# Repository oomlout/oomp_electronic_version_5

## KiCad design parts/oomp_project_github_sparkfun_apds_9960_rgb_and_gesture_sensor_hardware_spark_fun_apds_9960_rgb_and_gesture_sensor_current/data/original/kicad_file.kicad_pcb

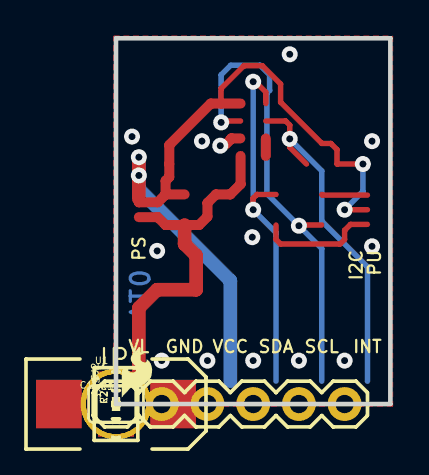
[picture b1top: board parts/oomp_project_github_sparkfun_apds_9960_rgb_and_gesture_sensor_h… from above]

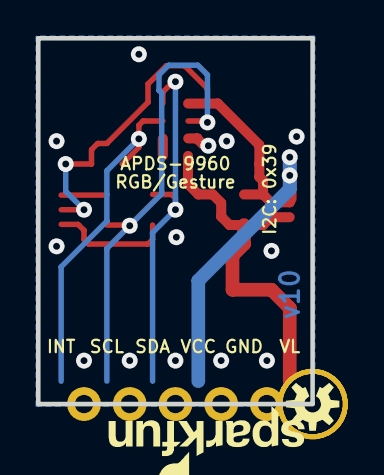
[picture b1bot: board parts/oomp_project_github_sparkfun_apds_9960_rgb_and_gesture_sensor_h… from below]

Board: 4 copper layers, 15.2 x 20.3 mm, 19 parts (2 on the bottom side), 9 nets.

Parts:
C1: 100uF; EIA7343
C2, C3: 1.0uF; 0603-CAP
FID1, FID2: FIDUCIAL1X2; FIDUCIAL-1X2
FRAME1: FRAME-LETTER; CREATIVE_COMMONS
JP1: 1X06
LOGO1: SFE_LOGO_FLAME.1_INCH; SFE_LOGO_FLAME_.1
LOGO2: OSHW-LOGOS; OSHW-LOGO-S
R1: 10k; 0603-RES
R2, R3: 4.7k; 0603
R4: DNP; 0603-RES
SJ1: SJ_3_PASTE1&2&3
SJ2: SOLDERJUMPERNC; SJ_2S
STANDOFF1, STANDOFF2: STAND-OFF
U1: APDS-9960
U$1: SFE_LOGO_NAME_FLAME.1_INCH; SFE_LOGO_NAME_FLAME_.1

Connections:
GND: C1.C, C2.2, C3.2, JP1.2, U1.6
INT: JP1.6, R1.1, U1.2
unnamed: R2.2, SJ1.3
unnamed: R3.2, SJ1.1
unnamed: U1.3, U1.4
SCL: JP1.5, R3.1, U1.7
SDA: JP1.4, R2.1, U1.1
VCC: C3.1, JP1.3, R1.2, R4.2, SJ1.2, SJ2.2, U1.8
VL: C1.A, C2.1, JP1.1, R4.1, SJ2.1, U1.5

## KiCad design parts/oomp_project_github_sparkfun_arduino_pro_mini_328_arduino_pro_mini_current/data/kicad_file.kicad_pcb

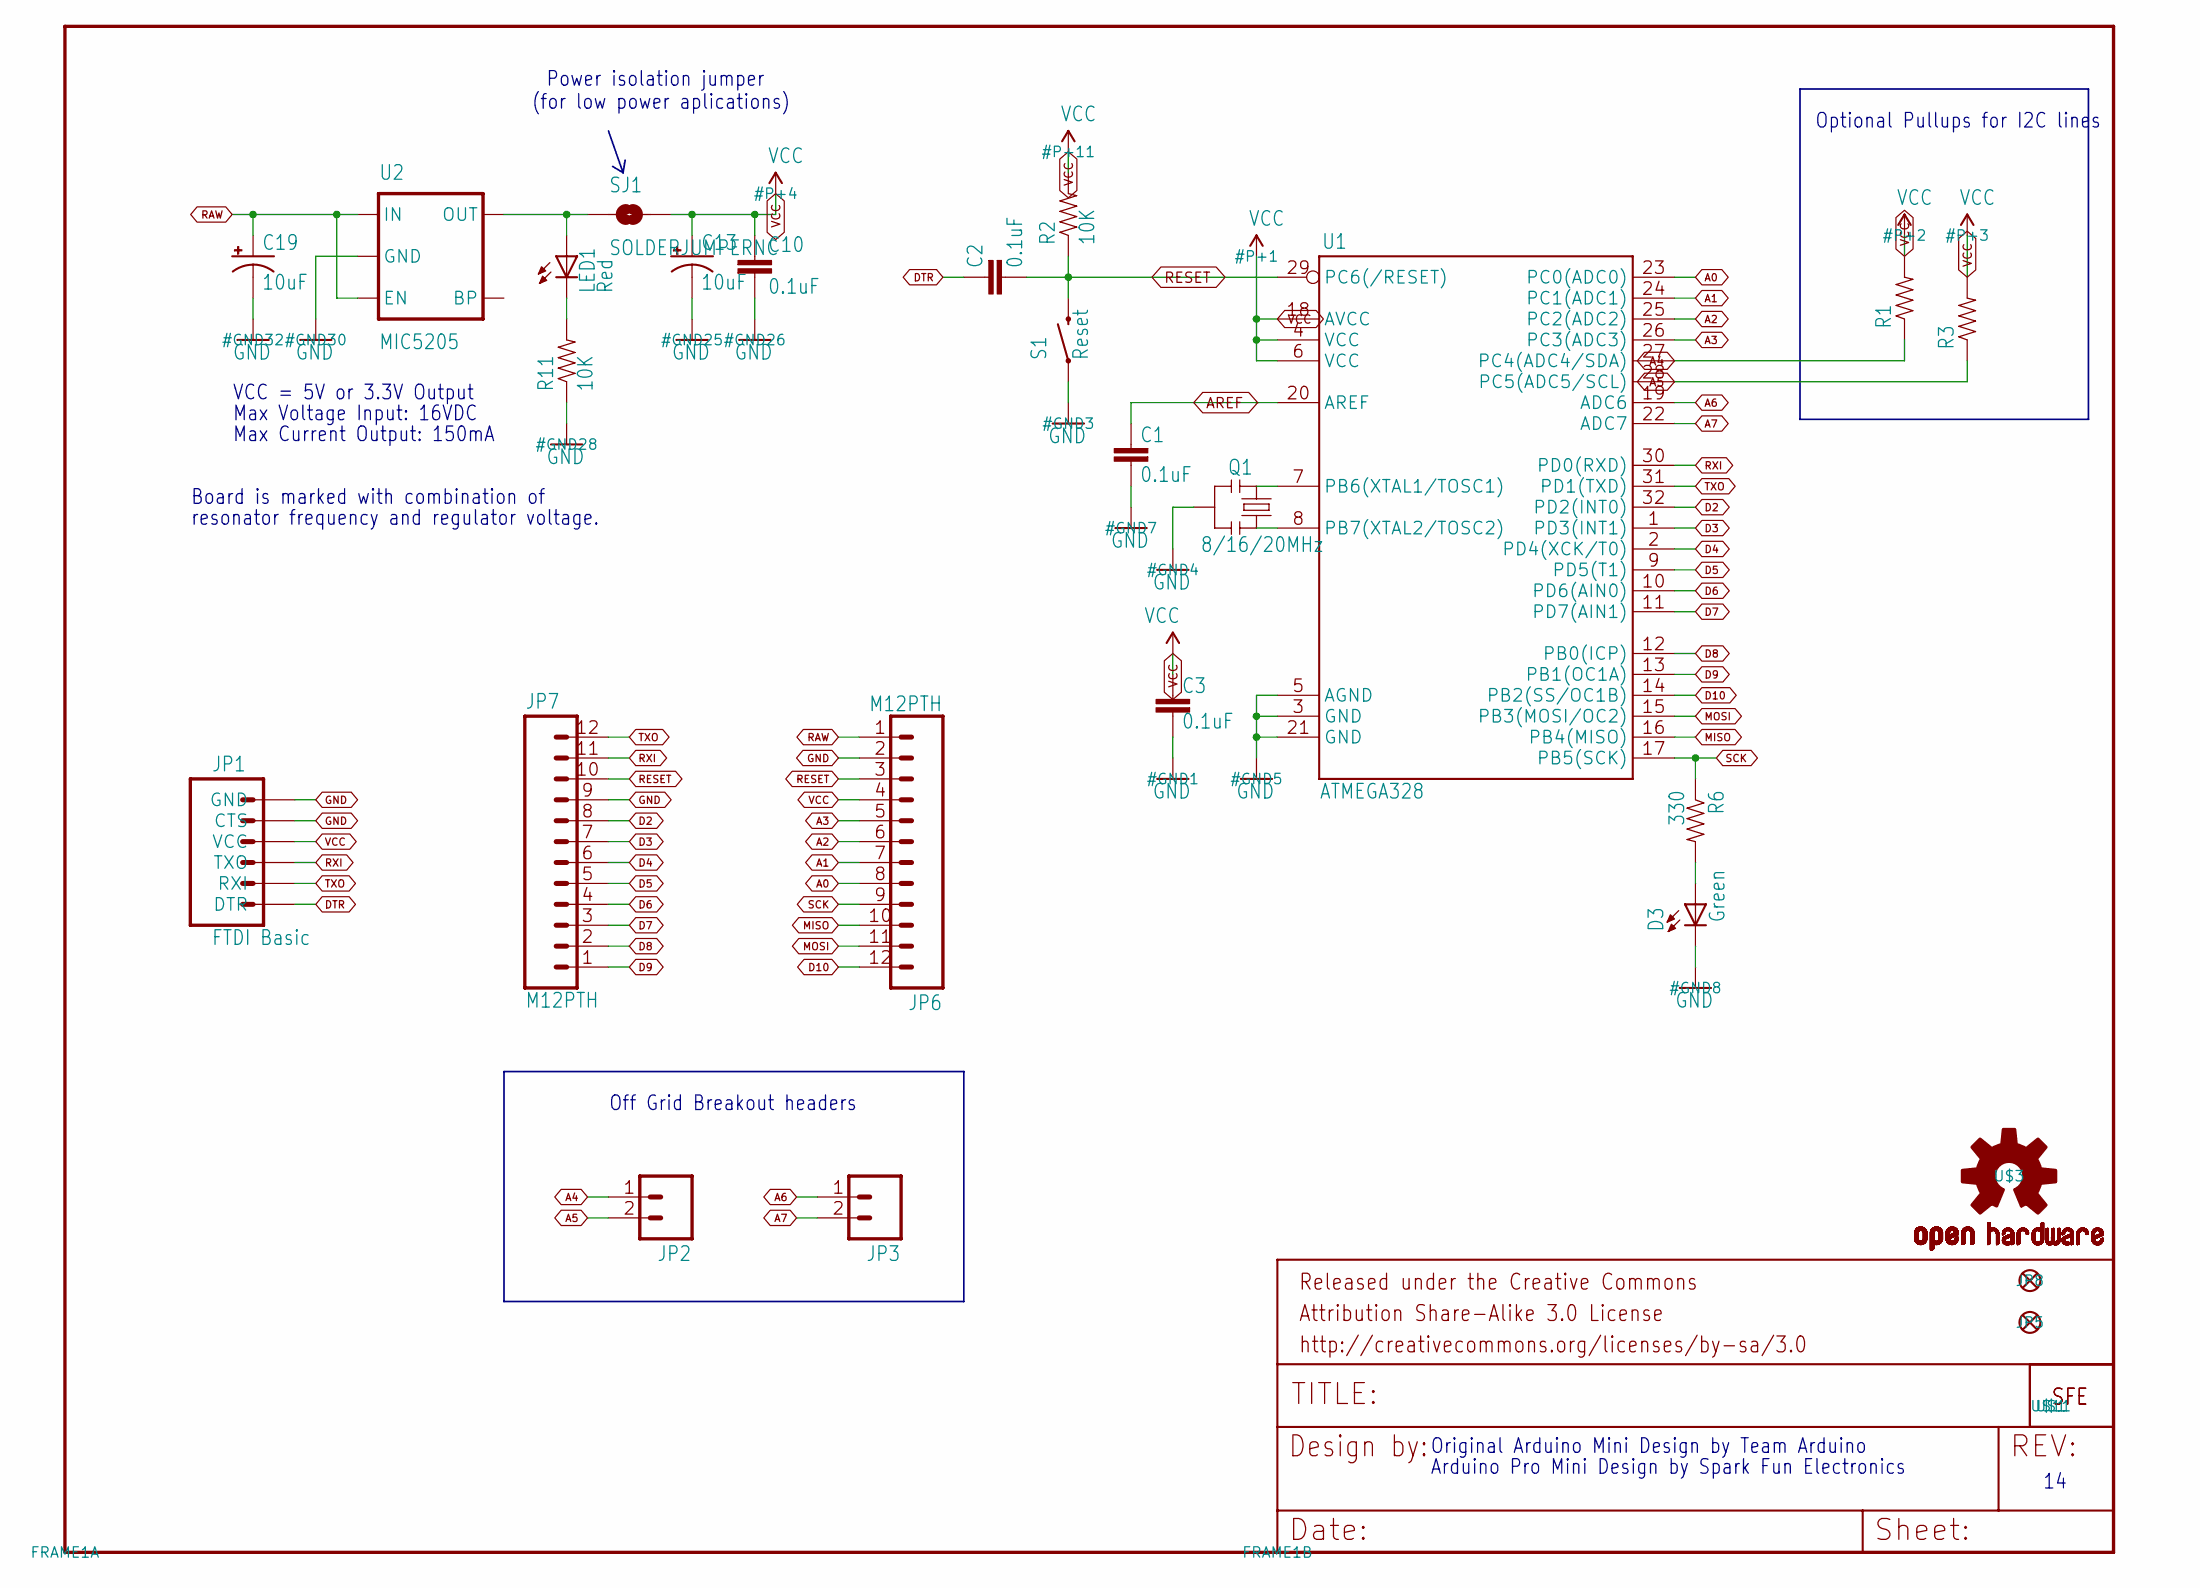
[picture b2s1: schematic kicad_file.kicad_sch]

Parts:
C1, C2, C3, C10: 0.1uF; 0603-CAP
C13, C19: 10uF; EIA3216
D3: Green; 0603-LED-ALT1
FRAME1: FRAME-LETTER; CREATIVE_COMMONS
JP1: FTDI Basic; 1X06
JP2, JP3: M02PTH; 1X02
JP5, JP8: FIDUCIALUFIDUCIAL; MICRO-FIDUCIAL
JP6, JP7: M12PTH; 1X12
LED1: Red; 0603-LED-ALT1
Q1: 8/16/20MHz; RESONATOR-SMD-1_1
R1, R3: RESISTOR0603-RES; 0603-RES
R2, R11: 10K; 0603-RES
R6: 330; 0603-RES
S1: Reset; TACTILE-SWITCH-SMD-ALT01
SJ1: SOLDERJUMPERNC; SJ_2S
U1: ATMEGA328; TQFP32-08
U2: MIC5205; SOT23-5
U$1: LOGO-SFESK; SFE-LOGO-FLAME
U$3: OSHW-LOGOS; OSHW-LOGO-S
U$11: LOGO-SFENEW; SFE-NEW-WEBLOGO

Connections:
A0: JP6.8, U1.23 (PC0(ADC0))
A1: JP6.7, U1.24 (PC1(ADC1))
A2: JP6.6, U1.25 (PC2(ADC2))
A3: JP6.5, U1.26 (PC3(ADC3))
A4: JP2.1, R1.1, U1.27 (PC4(ADC4/SDA))
A5: JP2.2, R3.1, U1.28 (PC5(ADC5/SCL))
A6: JP3.1, U1.19 (ADC6)
A7: JP3.2, U1.22 (ADC7)
AREF: C1.2, U1.20 (AREF)
D2: JP7.8, U1.32 (PD2(INT0))
D3: JP7.7, U1.1 (PD3(INT1))
D4: JP7.6, U1.2 (PD4(XCK/T0))
D5: JP7.5, U1.9 (PD5(T1))
D6: JP7.4, U1.10 (PD6(AIN0))
D7: JP7.3, U1.11 (PD7(AIN1))
D8: JP7.2, U1.12 (PB0(ICP))
D9: JP7.1, U1.13 (PB1(OC1A))
D10: JP6.12, U1.14 (PB2(SS/OC1B))
DTR: C2.2, JP1.1 (DTR)
GND: C1.1, C3.1, C10.2, C13.C (-), C19.C (-), D3.C, JP1.5 (CTS), JP1.6 (GND), JP6.2, JP7.9, Q1.2, R11.1, S1.1, S1.2 (1), U1.3 (GND), U1.5 (AGND), U1.21 (GND), U2.2 (GND)
MISO: JP6.10, U1.16 (PB4(MISO))
MOSI: JP6.11, U1.15 (PB3(MOSI/OC2))
unnamed: Q1.3, U1.8 (PB7(XTAL2/TOSC2))
unnamed: Q1.1, U1.7 (PB6(XTAL1/TOSC1))
unnamed: LED1.A, SJ1.1, U2.5 (OUT)
unnamed: LED1.C, R11.2
unnamed: D3.A, R6.2
RAW: C19.A (+), JP6.1, U2.1 (IN), U2.3 (EN)
RESET: C2.1, JP6.3, JP7.10, R2.1, S1.3 (2), S1.4 (2), U1.29 (PC6(/RESET))
RXI: JP1.3 (TXO), JP7.11, U1.30 (PD0(RXD))
SCK: JP6.9, R6.1, U1.17 (PB5(SCK))
TXO: JP1.2 (RXI), JP7.12, U1.31 (PD1(TXD))
VCC: C3.2, C10.1, C13.A (+), JP1.4 (VCC), JP6.4, R1.2, R2.2, R3.2, SJ1.2, U1.4 (VCC), U1.6 (VCC), U1.18 (AVCC)

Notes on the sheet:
Power isolation jumper
Off Grid Breakout headers
(for low power aplications)
VCC = 5V or 3.3V Output
Board is marked with combination of
Max Current Output: 150mA
Original Arduino Mini Design by Team Arduino
Max Voltage Input: 16VDC
resonator frequency and regulator voltage.
Arduino Pro Mini Design by Spark Fun Electronics
Optional Pullups for I2C lines

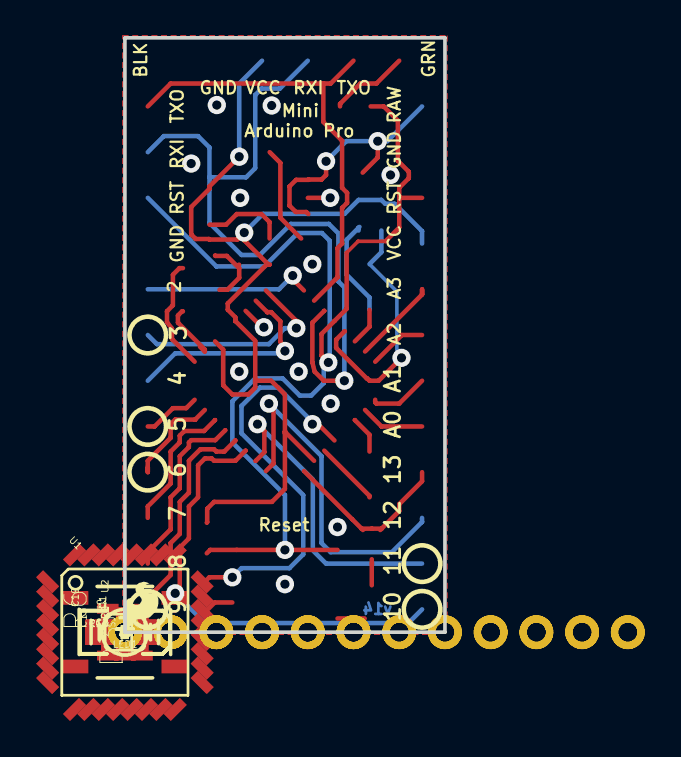
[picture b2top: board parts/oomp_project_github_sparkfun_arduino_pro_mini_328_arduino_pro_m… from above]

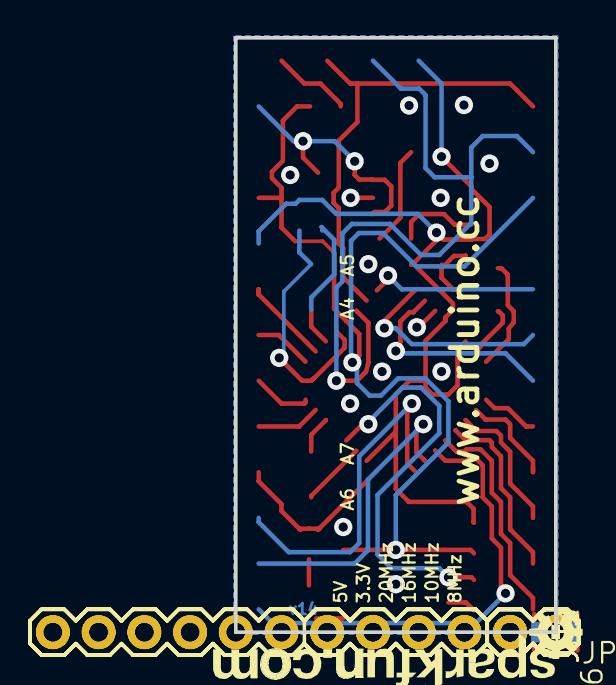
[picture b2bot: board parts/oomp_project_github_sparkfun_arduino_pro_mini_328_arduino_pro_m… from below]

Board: 2 copper layers, 17.8 x 33.0 mm, 29 parts (9 on the bottom side), 33 nets.

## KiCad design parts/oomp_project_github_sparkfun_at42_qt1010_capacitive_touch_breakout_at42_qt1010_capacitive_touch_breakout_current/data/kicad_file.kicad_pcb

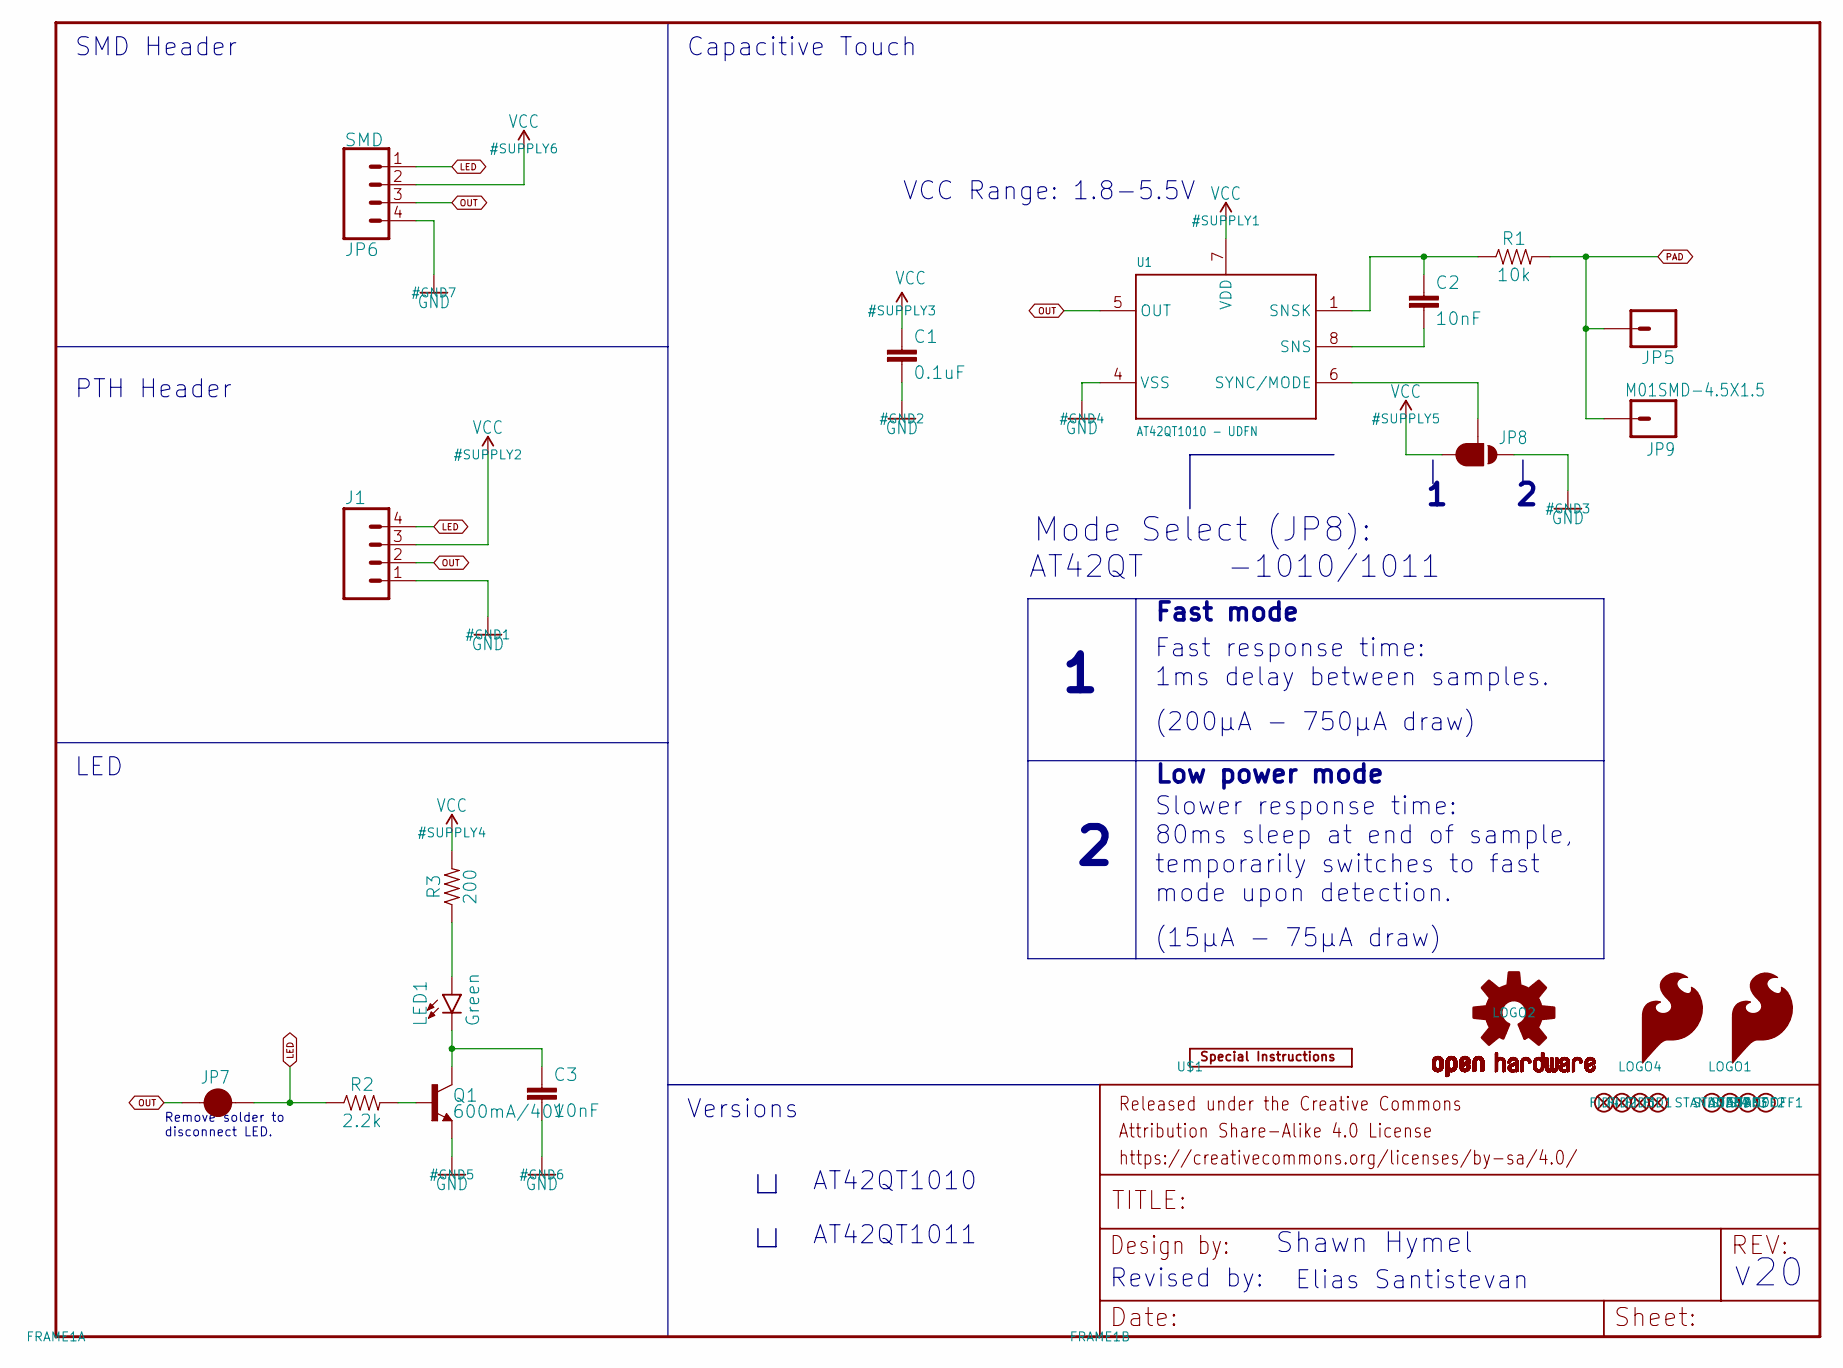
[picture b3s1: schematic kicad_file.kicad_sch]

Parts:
C1: 0.1uF; 0603
C2, C3: 10nF; 0603
FID1, FID2, FID3, FID4: FIDUCIAL1X2; FIDUCIAL-1X2
FRAME1: FRAME-LETTER; CREATIVE_COMMONS
J1: CONN_04; 1X04
JP5: CONN_01; 1X01
JP6: SMD; 1X04_SMD_RA_MALE
JP7: JUMPER-SMT_2_NC_PASTE_SILK; SMT-JUMPER_2_NC_PASTE_SILK
JP8: JUMPER-SMT_3_1-NC_PASTE_SILK; SMT-JUMPER_3_1-NC_PASTE_SILK
JP9: M01SMD-4.5X1.5; PAD-1.5X4.5
LED1: Green; LED-1206-BOTTOM
LOGO1, LOGO4: SFE_LOGO_FLAME.2_INCH; SFE_LOGO_FLAME_.2
LOGO2: OSHW-LOGOS; OSHW-LOGO-S
Q1: 600mA/40V; SOT23-3
R1: 10k; 0603
R2: 2.2k; 0603
R3: 200; 0603
STANDOFF1, STANDOFF2, STANDOFF3, STANDOFF4: STAND-OFF
U1: AT42QT1010 - UDFN; UDFN_USON_8_PAD
U$1: SPECIAL_INSTRUCTIONS-ORDERING; ORDERING_INSTRUCTIONS

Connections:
GND: C1.2, C3.2, J1.1, JP6.4, JP8.1, Q1.2 (E), U1.4 (VSS)
LED: J1.4, JP6.1, JP7.2, R2.1
unnamed: JP8.2, U1.6 (SYNC/MODE)
unnamed: C2.2, U1.8 (SNS)
unnamed: C2.1, R1.1, U1.1 (SNSK)
unnamed: Q1.1 (B), R2.2
unnamed: C3.1, LED1.C, Q1.3 (C)
unnamed: LED1.A, R3.1
OUT: J1.2, JP6.3, JP7.1, U1.5 (OUT)
PAD: JP5.1, JP9.P$1, R1.2
VCC: C1.1, J1.3, JP6.2, JP8.3, R3.2, U1.7 (VDD)

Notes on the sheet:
AT42QT1010
AT42QT1011
Revised by:
Slower response time: 80ms sleep at end of sample, temporarily switches to fast mode upon detection.
SMD Header
Mode Select (JP8):
PTH Header
Elias Santistevan
Capacitive Touch
Versions
Low power mode
(200µA - 750µA draw)
AT42QT
Remove solder to disconnect LED.
Fast response time: 1ms delay between samples.
v20
(15µA - 75µA draw)
Fast mode
LED
Shawn Hymel
-1010/1011
VCC Range: 1.8-5.5V

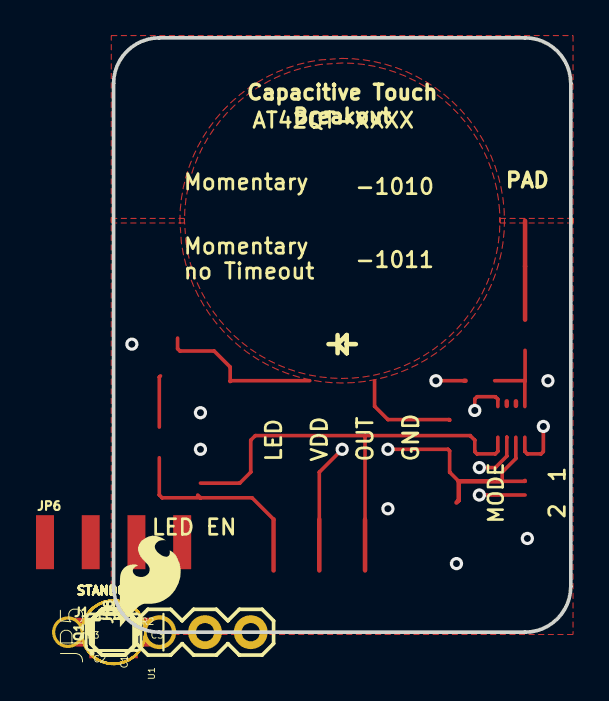
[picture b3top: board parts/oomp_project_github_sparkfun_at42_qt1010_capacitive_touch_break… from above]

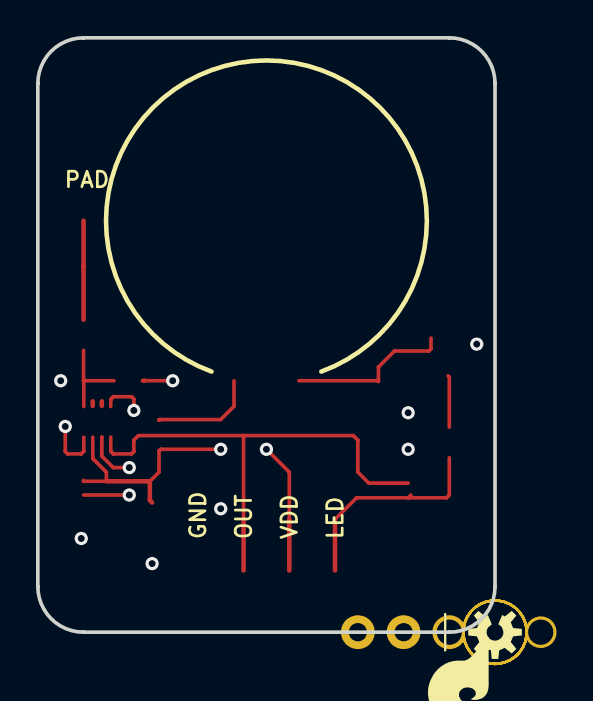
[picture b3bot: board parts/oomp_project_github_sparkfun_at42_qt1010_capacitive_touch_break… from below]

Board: 4 copper layers, 25.4 x 33.0 mm, 28 parts (4 on the bottom side), 11 nets.

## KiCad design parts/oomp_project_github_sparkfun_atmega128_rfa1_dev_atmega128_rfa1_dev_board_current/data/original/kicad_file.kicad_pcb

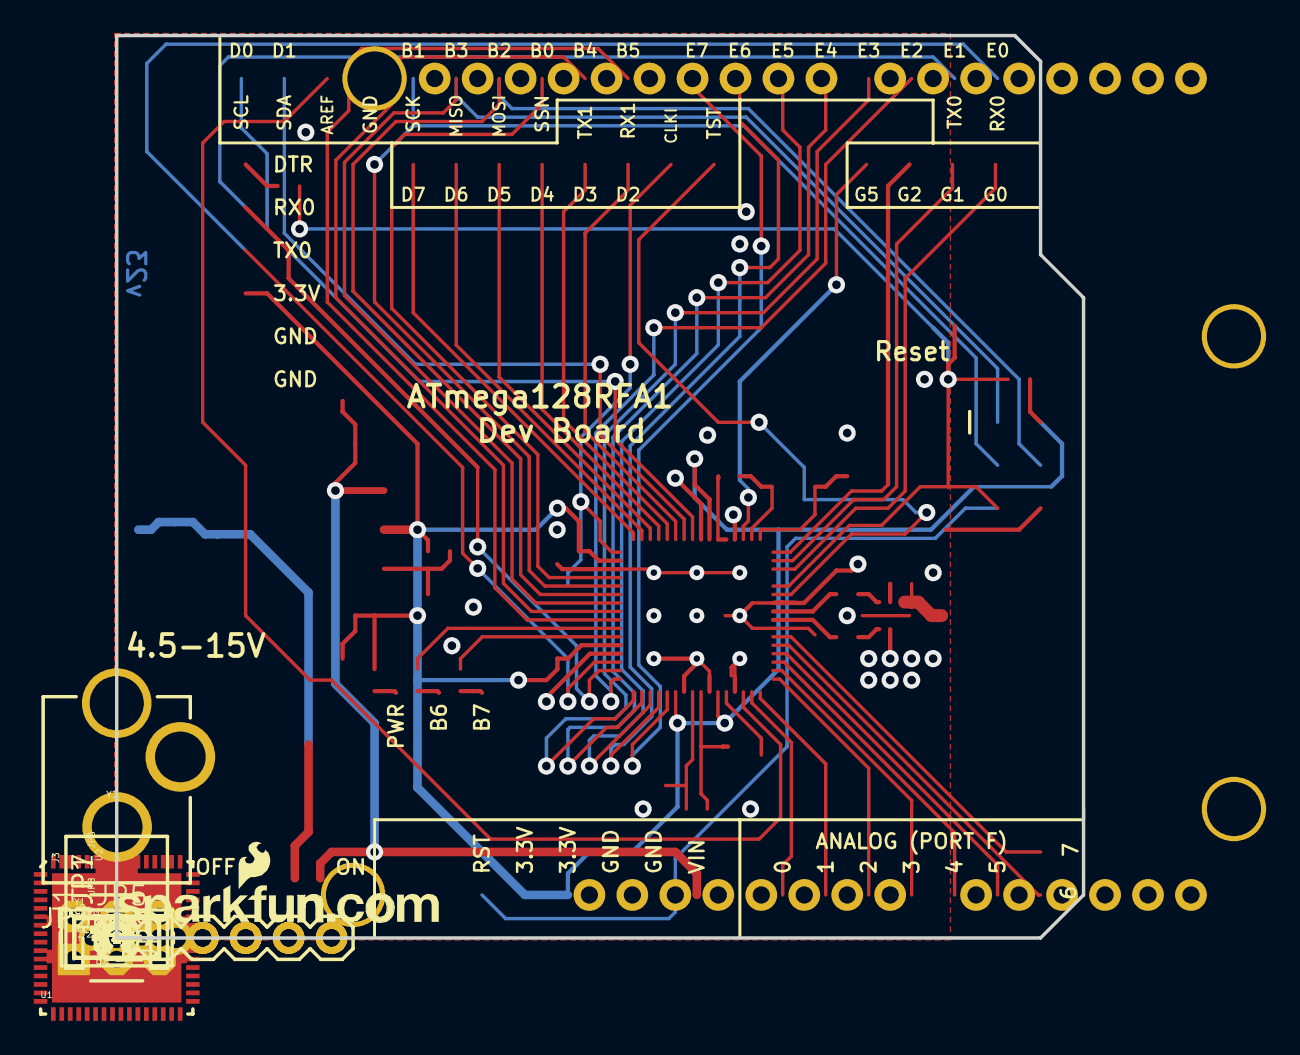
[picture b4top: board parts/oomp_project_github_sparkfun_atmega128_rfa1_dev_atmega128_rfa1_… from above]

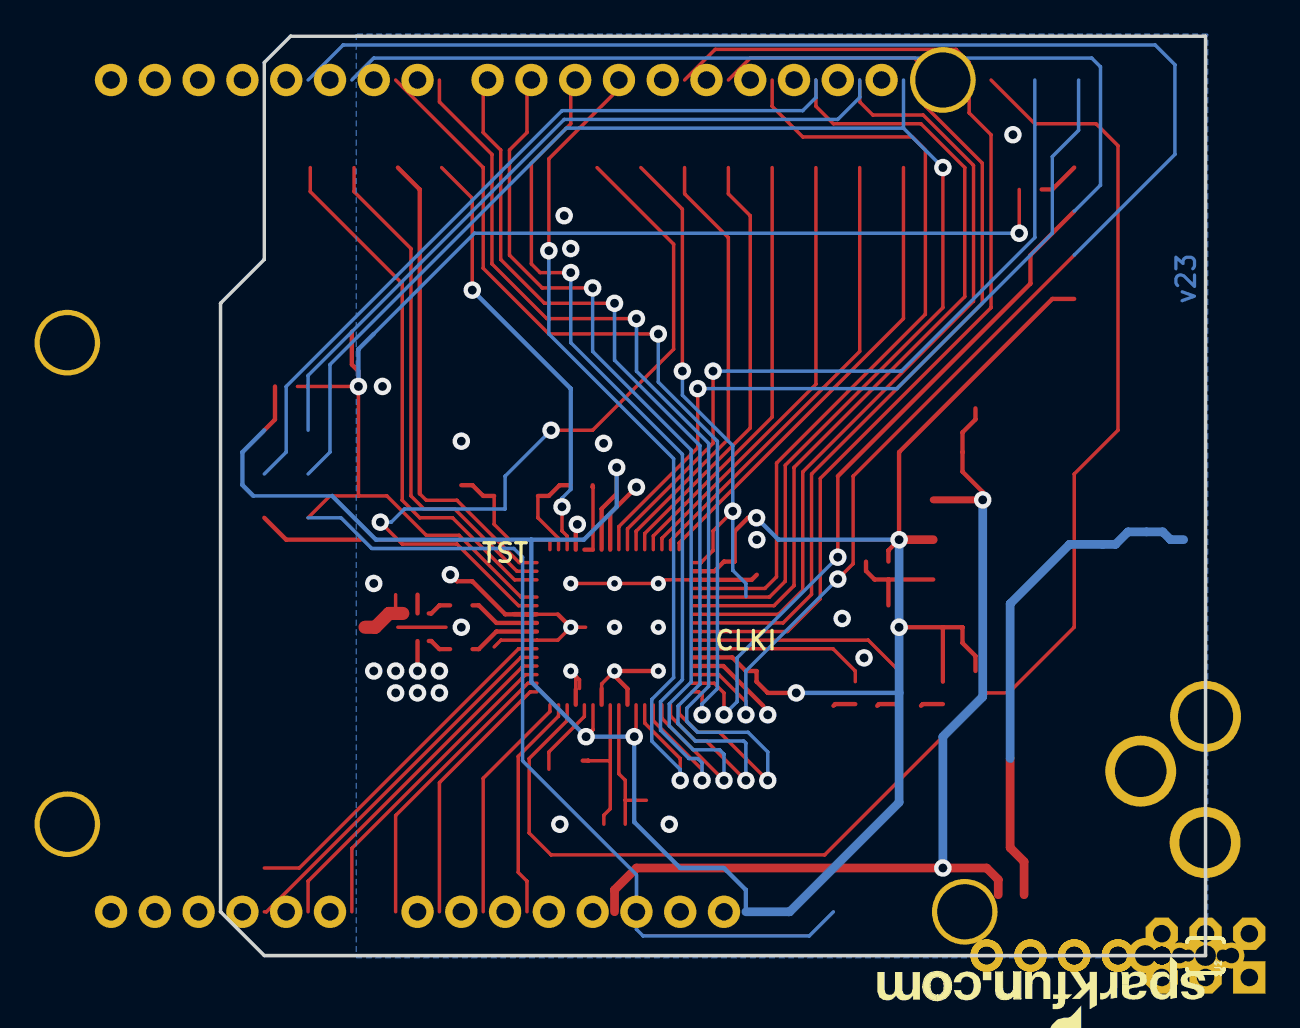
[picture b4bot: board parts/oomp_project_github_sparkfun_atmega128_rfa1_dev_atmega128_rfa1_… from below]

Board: 2 copper layers, 57.1 x 53.3 mm, 52 parts (3 on the bottom side), 61 nets.

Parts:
A1: ANTENNA2SMD5; ANTENNA-CHIP5
B1: 748421245; BALUN
C1, C2, C3, C4, C12: 1uF; 0402-CAP
C5, C6, C7, C8: 12pF; 0402-CAP
C9: 0.75pF; 0402-CAP
C10, C14: 10uF; EIA3216
C11: 22pF; 0402-CAP
C13, C15: 0.1uF; 0402-CAP
C16, C17: JUMP; 0402-CAP
FID1, FID2: FIDUCIALUFIDUCIAL; MICRO-FIDUCIAL
J1: ISP; 2X3-NS
J2: ARDUINO_UNO_R3
J3: POWER_JACKPTH_LOCK; POWER_JACK_PTH_LOCK
JP1, JP5, JP7: 1X02_NO_SILK
JP2: 1X04_NO_SILK
JP3: 1X06_NS
JP4, JP10: LOGO-SFENEW; SFE-NEW-WEBLOGO
JP6: JST-2-PTH
JP8: SCREWTERMINAL-3.5MM-2-NS
JP9: FTDI; FTDI_BASIC
LED1: RED; LED-0603
LED2, LED3: GREEN; LED-0603
R1: 10k; 0402-RES
R2: 1k; 0402-RES
R3: 240; 0402-RES
R4: 390; 0402-RES
R5, R6: 330; 0402-RES
S1: TACTILE_SWITCH_SMD
S2: SWITCH-SPST-SMD-A
SJ1, SJ2: SJ_2S-TRACE
U1: ATMEGA128RFA1; QFN-64
U2: LM1117; SOT223
U$1: OSHW-LOGOS; OSHW-LOGO-S
Y1: 16MHz; CRYSTAL-SMD-5X3
Y2: 32.768kHz; CRYSTAL-32KHZ-SMD

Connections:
3.3V: C3.1, C4.1, C10.A, C12.1, J1.2, J2.3.3V, J2.5V, JP9.VCC, R1.2, R2.2, R3.2, U1.23, U1.34, U1.44, U1.54, U1.59, U2.2
A0: J2.A0, U1.63
A1: J2.A1, U1.64
A2: J2.A2, U1.1
A3: J2.A3, U1.2
A4: J2.A4, U1.3
A5: J2.A5, U1.4
A6: JP1.1, U1.5
A7: JP1.2, U1.6
AREF: J2.AREF, U1.62
AVDD: C1.1, U1.60
CLKI: JP5.1, SJ1.2, U1.33
DTR: C15.1, JP9.DTR
DVDD: C2.1, U1.21, U1.22
FB: R3.1, R4.2, U2.1
GND: B1.5, C1.2, C2.2, C3.2, C4.2, C5.2, C6.2, C7.2, C8.2, C9.1, C10.C, C11.2, C12.2, C13.2, C14.C, J1.6, J2.GND@0, J2.GND@1, J2.GND@2, J3.GND, J3.GNDBREAK, JP6.1, JP7.1, JP8.1, JP9.GND, LED1.C, LED2.C, LED3.C, R4.1, S1.3, SJ1.1, SJ2.1, U1.7, U1.10, U1.20, U1.24, U1.35, U1.45, U1.55, U1.58, U1.61, U1.65
MISO: J1.1, J2.D12, U1.39
MOSI: J1.4, J2.D11, U1.38
unnamed: LED1.A, R2.1
unnamed: C5.1, U1.57, Y1.3
unnamed: C6.1, U1.56, Y1.1
unnamed: C7.1, U1.18, Y2.X1
unnamed: C8.1, U1.17, Y2.X2
unnamed: B1.2, C11.1
unnamed: LED3.A, R5.1
unnamed: J3.PWR, JP6.2, JP7.2, JP8.2, S2.2
unnamed: B1.4, C16.2
unnamed: B1.3, C17.1
unnamed: LED2.A, R6.1
PB4: J2.D9, U1.40
PB5: J2.D8, U1.41
PB6: R5.2, U1.42
PB7: R6.2, U1.43
PD4: JP3.3, U1.29
PD5: JP3.4, U1.30
PD6: JP3.5, U1.31
PD7: JP3.6, U1.32
PE2: J2.D2, U1.48
PE3: J2.D3, U1.49
PE4: J2.D4, U1.50
PE5: J2.D5, U1.51
PE6: J2.D6, U1.52
PE7: J2.D7, U1.53
PG0: JP2.1, U1.14
PG1: JP2.2, U1.15
PG2: JP2.3, U1.16
PG5: JP2.4, U1.19
RESET: C15.2, J1.5, J2.RES, R1.1, S1.1, U1.12
RFANT: A1.FEED, B1.1, C9.2
RFN: C17.2, U1.9
RFP: C16.1, U1.8
RX0: J2.RX, JP9.TXO, U1.46
RX1: JP3.1, U1.27
SCK: J1.3, J2.D13, U1.37
SCL: J2.SCL, U1.25
SDA: J2.SDA, U1.26
SSN: J2.D10, U1.36
TST: JP5.2, SJ2.2, U1.11
TX0: J2.TX, JP9.RXI, U1.47
TX1: JP3.2, U1.28
VCC: C13.1, C14.A, J2.VIN, S2.1, U2.3

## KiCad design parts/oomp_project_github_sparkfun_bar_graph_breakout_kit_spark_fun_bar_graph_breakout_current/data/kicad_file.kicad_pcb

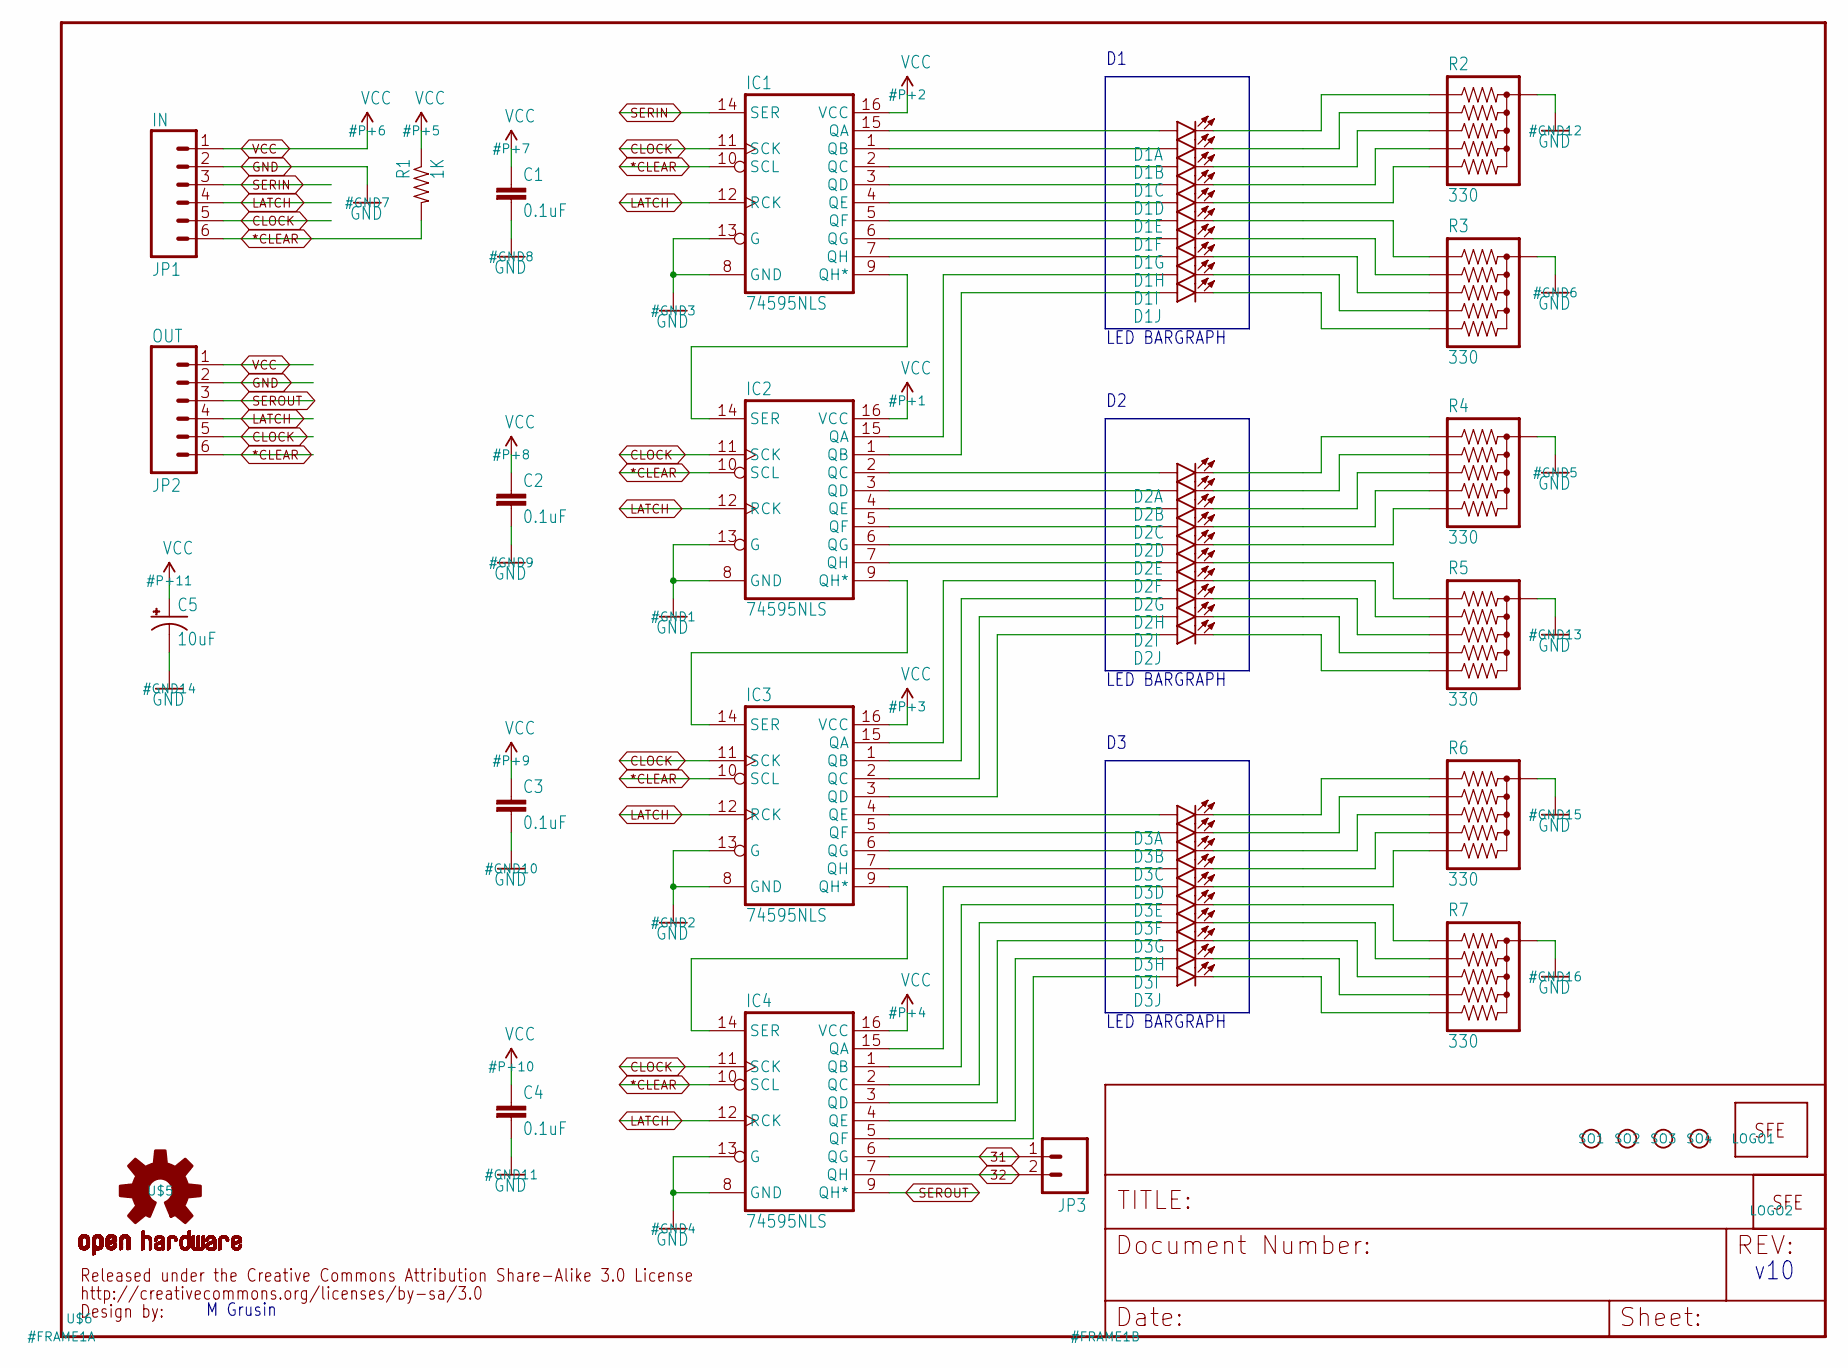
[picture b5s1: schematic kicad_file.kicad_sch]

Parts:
C1, C2, C3, C4: 0.1uF; CAP-PTH-SMALL2
C5: 10uF; CPOL-RADIAL-10UF-25V
D1, D2, D3: LED_BARGRAPH_10; LED_BARGAPH_10
IC1, IC2, IC3, IC4: 74595NLS; DIL16
JP1: IN; 1X06
JP2: OUT; 1X06
JP3: M02PTH; 1X02
LOGO1: LOGO-SFENW2; SFE-NEW-WEB
LOGO2: LOGO-SFESK; SFE-LOGO-FLAME
R1: 1K; AXIAL-0.3
R2, R3, R4, R5, R6, R7: 330; RPACK-SIP-PTH-5
SO1, SO2, SO3, SO4: STAND-OFF
U$5: OSHW-LOGOM; OSHW-LOGO-M
U$6: CREATIVE_COMMONS

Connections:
31: IC4.6 (QG), JP3.1
32: IC4.7 (QH), JP3.2
*CLEAR: IC1.10 (SCL), IC2.10 (SCL), IC3.10 (SCL), IC4.10 (SCL), JP1.6, JP2.6, R1.P$2 (2)
CLOCK: IC1.11 (SCK), IC2.11 (SCK), IC3.11 (SCK), IC4.11 (SCK), JP1.5, JP2.5
GND: C1.2, C2.2, C3.2, C4.2, C5.2 (-), IC1.8 (GND), IC1.13 (G), IC2.8 (GND), IC2.13 (G), IC3.8 (GND), IC3.13 (G), IC4.8 (GND), IC4.13 (G), JP1.2, JP2.2, R2.P$1 (1), R3.P$1 (1), R4.P$1 (1), R5.P$1 (1), R6.P$1 (1), R7.P$1 (1)
LATCH: IC1.12 (RCK), IC2.12 (RCK), IC3.12 (RCK), IC4.12 (RCK), JP1.4, JP2.4
unnamed: D1.1 (A), IC1.15 (QA)
unnamed: D1.2 (A), IC1.1 (QB)
unnamed: D1.3 (A), IC1.2 (QC)
unnamed: D1.4 (A), IC1.3 (QD)
unnamed: D1.5 (A), IC1.4 (QE)
unnamed: D1.6 (A), IC1.5 (QF)
unnamed: D1.7 (A), IC1.6 (QG)
unnamed: D1.8 (A), IC1.7 (QH)
unnamed: D1.9 (A), IC2.15 (QA)
unnamed: D1.10 (A), IC2.1 (QB)
unnamed: D2.8 (A), IC3.1 (QB)
unnamed: D2.7 (A), IC3.15 (QA)
unnamed: D2.9 (A), IC3.2 (QC)
unnamed: D2.10 (A), IC3.3 (QD)
unnamed: D3.1 (A), IC3.4 (QE)
unnamed: D3.2 (A), IC3.5 (QF)
unnamed: D3.3 (A), IC3.6 (QG)
unnamed: D3.4 (A), IC3.7 (QH)
unnamed: D2.1 (A), IC2.2 (QC)
unnamed: D2.2 (A), IC2.3 (QD)
unnamed: D2.3 (A), IC2.4 (QE)
unnamed: D2.4 (A), IC2.5 (QF)
unnamed: D2.5 (A), IC2.6 (QG)
unnamed: D2.6 (A), IC2.7 (QH)
unnamed: D1.20 (C), R2.P$2 (2)
unnamed: D1.19 (C), R2.P$3 (3)
unnamed: D3.5 (A), IC4.15 (QA)
unnamed: D3.6 (A), IC4.1 (QB)
unnamed: D1.18 (C), R2.P$4 (4)
unnamed: D1.17 (C), R2.P$5 (5)
unnamed: D1.16 (C), R2.P$6 (6)
unnamed: D1.15 (C), R3.P$2 (2)
unnamed: D1.14 (C), R3.P$3 (3)
unnamed: D1.13 (C), R3.P$4 (4)
unnamed: D1.12 (C), R3.P$5 (5)
unnamed: D1.11 (C), R3.P$6 (6)
unnamed: D2.20 (C), R4.P$2 (2)
unnamed: D2.19 (C), R4.P$3 (3)
unnamed: D3.7 (A), IC4.2 (QC)
unnamed: D3.8 (A), IC4.3 (QD)
unnamed: D3.9 (A), IC4.4 (QE)
unnamed: D3.10 (A), IC4.5 (QF)
unnamed: D2.18 (C), R4.P$4 (4)
unnamed: D2.17 (C), R4.P$5 (5)
unnamed: D2.16 (C), R4.P$6 (6)
unnamed: D2.15 (C), R5.P$2 (2)
unnamed: D2.14 (C), R5.P$3 (3)
unnamed: D2.13 (C), R5.P$4 (4)
unnamed: D2.12 (C), R5.P$5 (5)
unnamed: D2.11 (C), R5.P$6 (6)
unnamed: D3.20 (C), R6.P$2 (2)
unnamed: D3.19 (C), R6.P$3 (3)
unnamed: D3.18 (C), R6.P$4 (4)
unnamed: D3.17 (C), R6.P$5 (5)
unnamed: D3.16 (C), R6.P$6 (6)
unnamed: D3.15 (C), R7.P$2 (2)
unnamed: D3.14 (C), R7.P$3 (3)
unnamed: D3.13 (C), R7.P$4 (4)
unnamed: D3.12 (C), R7.P$5 (5)
unnamed: D3.11 (C), R7.P$6 (6)
unnamed: IC1.9 (QH*), IC2.14 (SER)
unnamed: IC2.9 (QH*), IC3.14 (SER)
unnamed: IC3.9 (QH*), IC4.14 (SER)
SERIN: IC1.14 (SER), JP1.3
SEROUT: IC4.9 (QH*), JP2.3
VCC: C1.1, C2.1, C3.1, C4.1, C5.1 (+), IC1.16 (VCC), IC2.16 (VCC), IC3.16 (VCC), IC4.16 (VCC), JP1.1, JP2.1, R1.P$1 (1)

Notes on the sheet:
M Grusin
LED BARGRAPH
v10

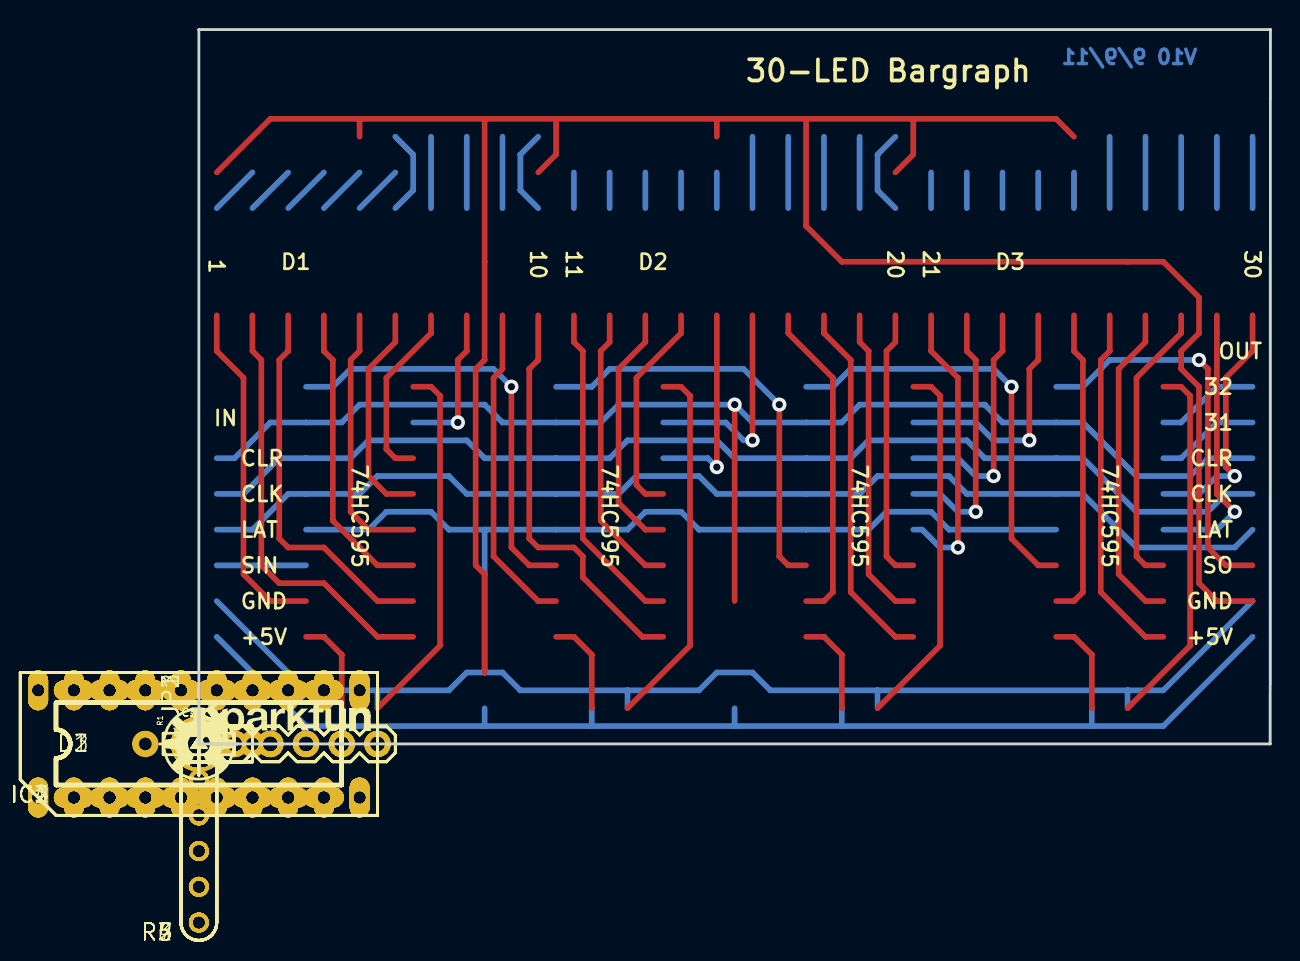
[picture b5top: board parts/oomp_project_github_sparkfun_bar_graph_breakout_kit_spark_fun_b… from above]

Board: 2 copper layers, 76.2 x 50.8 mm, 30 parts (0 on the bottom side), 72 nets.

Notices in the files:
parts/oomp_project_github_sparkfun_arduino_pro_mini_328_arduino_pro_mini_current/data/kicad_file.kicad_sch:
Released under the Creative Commons
http://creativecommons.org/licenses/by-sa/3.0
parts/oomp_project_github_sparkfun_at42_qt1010_capacitive_touch_breakout_at42_qt1010_capacitive_touch_breakout_current/data/original/kicad_file.kicad_sch:
https://creativecommons.org/licenses/by-sa/4.0
parts/oomp_project_github_sparkfun_bar_graph_breakout_kit_spark_fun_bar_graph_breakout_current/data/kicad_file.kicad_sch:
Released under the Creative Commons Attribution Share-Alike 3.0 License
